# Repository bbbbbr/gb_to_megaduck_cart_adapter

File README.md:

# Game Boy to MegaDuck Cart Slot Adapter
Design files for a plug-in adapter to use Game Boy cartridges on a MegaDuck console.

The consoles have near identical cpu cores (1) and an almost identical cart pinout but a different edge connector style (Game Boy: one-sided, MegaDuck double-sided) and different cartridge widths (MegaDuck cart slot is narrower). This adapter allows plugging GB carts into the MegaDuck Console.

*1. But with modified register addresses, values and other changes to make the MegaDuck incompatible.

# Game Boy game compatibility
- **Q:** Does this mean regular Game Boy carts/games will run unmodified on the Mega Duck with this adapter?
- **A:** __No.__ Game Boy games require manual ROM patching to alter their register addresses, values and other changes in order to run on the Mega Duck.

# Why?
Flash carts for the Game Boy are easier to obtain and are available with a wider variety of features than those for the MegaDuck. Having access to the full range of GB flash carts opens up a lot of options for Mega Duck homebrew development, research and testing. This includes Game Boy Cameras modified to allow running custom ROMs run on them.

# Cartridge Shell
The following 3D printable cartidge shell design can be used with this adapter if the top edge of it is either removed from the design before printing or manually trimmed after printing.

https://github.com/bbbbbr/megaduck_cartridge_shell

TODO: Make cart shell specicially meant for this adapter

# Riser Height
The design has been built with **11mm risers** which provides enough clearance to plug in a some [GB Interceptor](https://github.com/bbbbbr/megaduck-interceptor) builds.

Riser heights down to **3.5mm - 4mm** should work and would result in a much smaller gap between the cart and the back of the console.

# License
Per the LICENSE file this design is released into the public domain and no attribution is required.

# Credits & Thanks
Thanks to Sean Riddle, Nitro2k, TexElec (pcb design)

# Alternate Top Board for Game Boy Camera
A different top board that allows using a regular Game Boy Camera Shell (modified ROM still required) is also available.
It changes the orientation so the Game Boy cart connector is facing UP.

The design is by Raphaël Boichot: https://github.com/Raphael-Boichot/Megaduck-to-game-boy-camera-adapter

# Pix

# GB to MegaDuck Cart Edge Connector Pinout Mapping

| **Mega Duck Cart Side** | **Pin Num** | **GB/DMG Pin** | **Mega Duck Pin** |
| ----------------------- | ----------- | -------------- | ----------------- |
| top                     | 1           | VCC            | +5 VDC            |
| bottom                  | 2           | CLK            | CLK               |
| top                     | 3           | /WR            | /WR               |
| bottom                  | 4           | /RD            | /RD               |
| top                     | 5           | CS             | CS                |
| bottom                  | 6           | A0             | A0                |
| top                     | 7           | A1             | A1                |
| bottom                  | 8           | A2             | A2                |
| top                     | 9           | A3             | A3                |
| bottom                  | 10          | A4             | A4                |
| top                     | 11          | A5             | A5                |
| bottom                  | 12          | A6             | A6                |
| top                     | 13          | A7             | A7                |
| bottom                  | 14          | A8             | A8                |
| top                     | 15          | A9             | A9                |
| bottom                  | 16          | A10            | A10               |
| top                     | 17          | A11            | A11               |
| bottom                  | 18          | A12            | A12               |
| top                     | 19          | A13            | A13               |
| bottom                  | 20          | A14            | A14               |
| top                     | 21          | A15            | A15               |
| bottom                  | 22          | D0             | D0                |
| top                     | 23          | D1             | D1                |
| bottom                  | 24          | D2             | D2                |
| top                     | 25          | D3             | D3                |
| bottom                  | 26          | D4             | D4                |
| top                     | 27          | D5             | D5                |
| bottom                  | 28          | D6             | D6                |
| top                     | 29          | D7             | D7                |
| bottom                  | 30          | /RST           | /RST              |
| top                     | 31          | VIN            | NC                |
| bottom                  | 32          | GND            | NC                |
| top                     | 33          | \-             | NC                |
| bottom                  | 34          | \-             | NC                |
| top                     | 35          | \-             | GND               |
| bottom                  | 36          | \-             | GND               |

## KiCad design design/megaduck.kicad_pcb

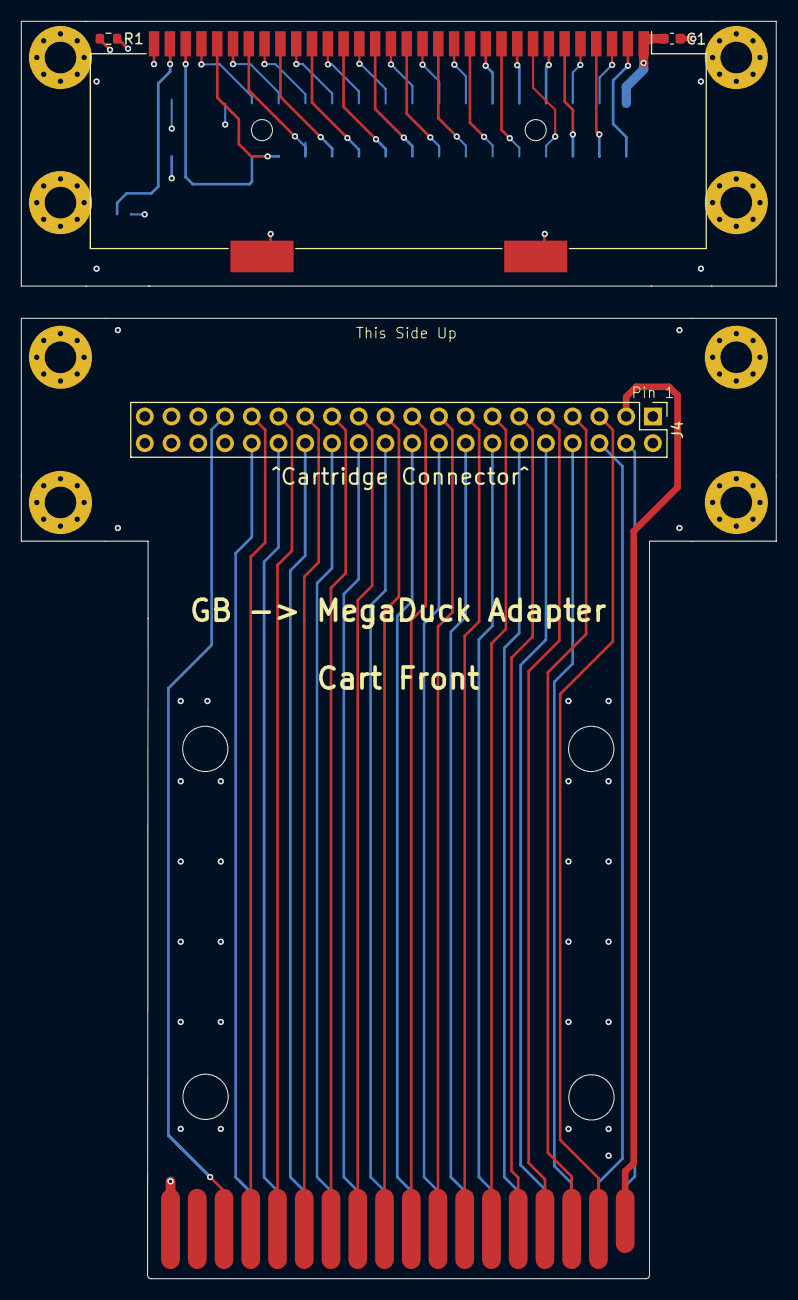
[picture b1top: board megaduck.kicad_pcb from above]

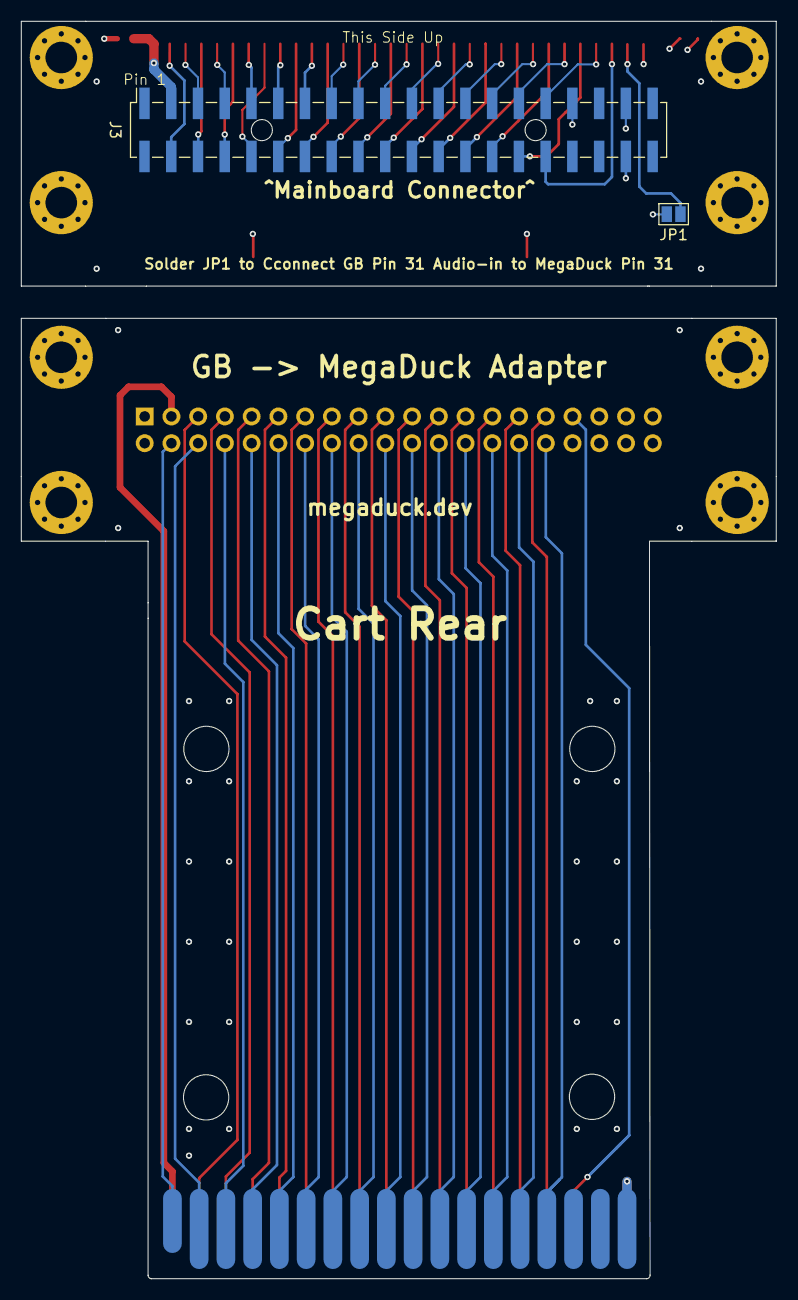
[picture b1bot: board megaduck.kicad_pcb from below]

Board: 4 copper layers, 71.7 x 119.4 mm, 15 parts (2 on the bottom side), 33 nets.

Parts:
C1: 0.1uf; C_0603_1608Metric
H1, H2, H3, H4, H5, H6, H7, H8: MountingHole_Pad; MountingHole_3mm_Pad_Via
J1: Conn_02x18_Odd_Even; Mega_Duck_36_Pin
J3: GameBoy_Cartridge_MountingPin; GameBoy_Cartridge_AGS_1x32-1MP_P1.50mm_Socket_Horizontal
J3#2: Conn_02x20_Odd_Even; PinSocket_2x20_P2.54mm_Vertical_SMD
J4: Conn_02x20_Odd_Even; PinHeader_2x20_P2.54mm_Vertical
JP1: SolderJumper_2_Open; SolderJumper-2_P1.3mm_Open_Pad1.0x1.5mm
R1: 100k; R_0603_1608Metric

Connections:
/A0: J1.6, J3.6 (A0), J3#2.8, J4.8
/A1: J1.7, J3.7 (A1), J3#2.9, J4.9
/A2: J1.8, J3.8 (A2), J3#2.10, J4.10
/A3: J1.9, J3.9 (A3), J3#2.11, J4.11
/A4: J1.10, J3.10 (A4), J3#2.12, J4.12
/A5: J1.11, J3.11 (A5), J3#2.13, J4.13
/A6: J1.12, J3.12 (A6), J3#2.14, J4.14
/A7: J1.13, J3.13 (A7), J3#2.15, J4.15
/A8: J1.14, J3.14 (A8), J3#2.16, J4.16
/A9: J1.15, J3.15 (A9), J3#2.17, J4.17
/A10: J1.16, J3.16 (A10), J3#2.18, J4.18
/A11: J1.17, J3.17 (A11), J3#2.19, J4.19
/A12: J1.18, J3.18 (A12), J3#2.20, J4.20
/A13: J1.19, J3.19 (A13), J3#2.21, J4.21
/A14: J1.20, J3.20 (A14), J3#2.22, J4.22
/A15: J1.21, J3.21 (A15), J3#2.23, J4.23
/D0: J1.22, J3.22 (D0), J3#2.24, J4.24
/D1: J1.23, J3.23 (D1), J3#2.25, J4.25
/D2: J1.24, J3.24 (D2), J3#2.26, J4.26
/D3: J1.25, J3.25 (D3), J3#2.27, J4.27
/D4: J1.26, J3.26 (D4), J3#2.28, J4.28
/D5: J1.27, J3.27 (D5), J3#2.29, J4.29
/D6: J1.28, J3.28 (D6), J3#2.30, J4.30
/D7: J1.29, J3.29 (D7), J3#2.31, J4.31
/PHI: J1.2, J3.2 (PHI), J3#2.4, J4.4
/VCC: C1.1, J1.1, J3.1 (VCC), J3#2.3, J4.3, R1.1
/VIN+: J1.31, J3#2.33, J4.33, JP1.1 (A)
/~CS: J1.5, J3.5 (~CS), J3#2.7, J4.7
/~RD: J1.4, J3.4 (~RD), J3#2.6, J4.6
/~RES: J1.30, J3.30 (~RES), J3#2.32, J4.32, R1.2
/~WR: J1.3, J3.3 (~WR), J3#2.5, J4.5
GND: C1.2, H1.1, H2.1, H3.1, H4.1, H5.1, H6.1, H7.1, H8.1, J1.35, J1.36, J3.32 (GND), J3.MP, J3#2.37, J3#2.38, J4.37, J4.38
unnamed: J3.31 (VIN), JP1.2 (B)

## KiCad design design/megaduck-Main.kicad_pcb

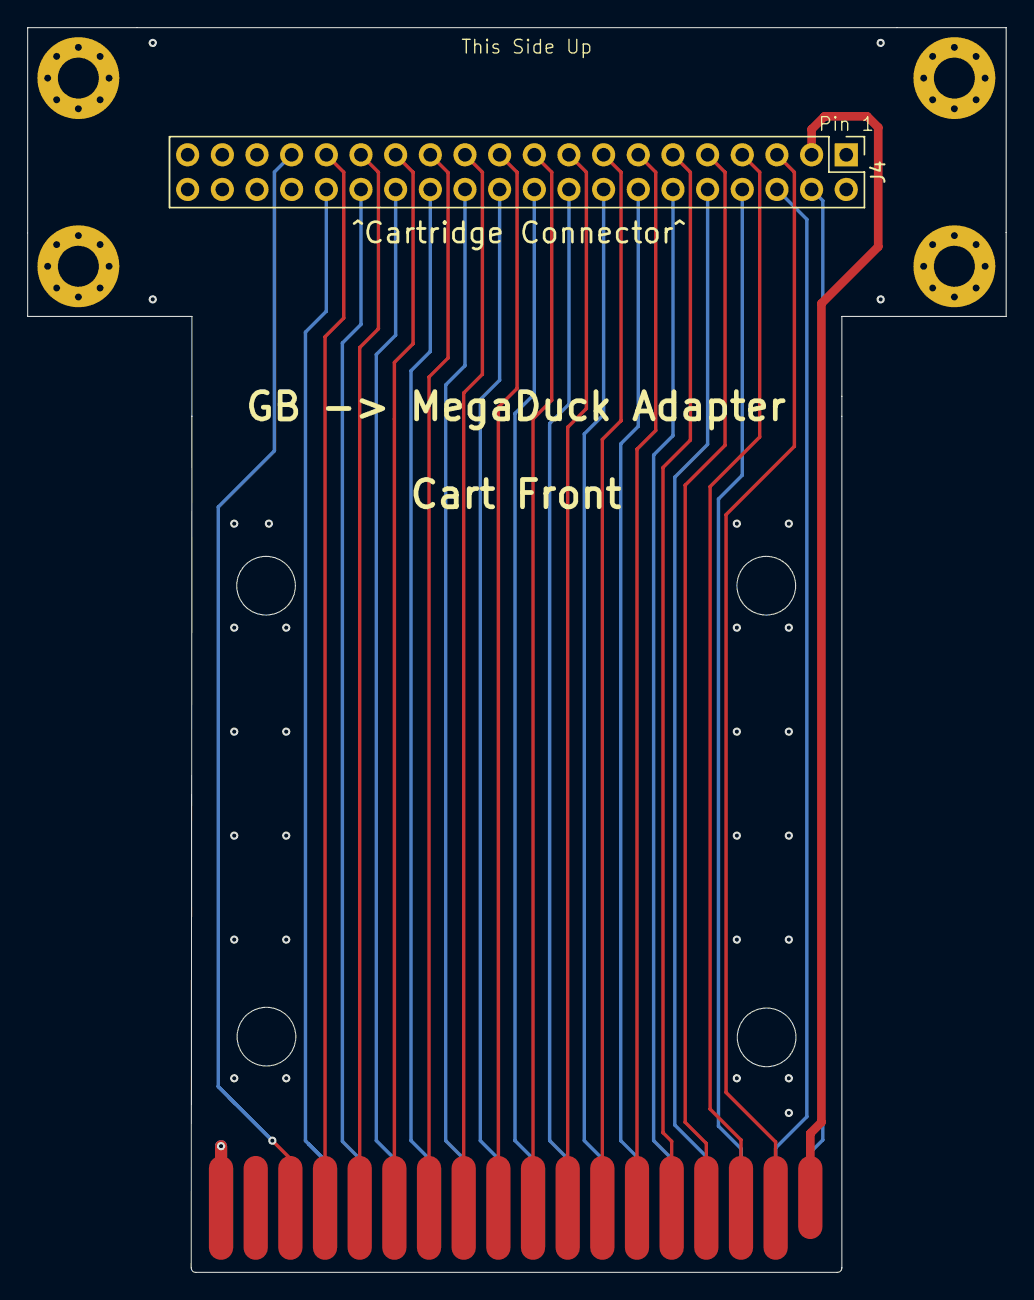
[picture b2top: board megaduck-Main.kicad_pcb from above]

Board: 4 copper layers, 71.7 x 91.2 mm, 6 parts (0 on the bottom side), 32 nets.

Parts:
H3, H4, H7, H8: MountingHole_Pad; MountingHole_3mm_Pad_Via
J1: Conn_02x18_Odd_Even; Mega_Duck_36_Pin
J4: Conn_02x20_Odd_Even; PinHeader_2x20_P2.54mm_Vertical

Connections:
/A0: J1.6, J4.8
/A1: J1.7, J4.9
/A2: J1.8, J4.10
/A3: J1.9, J4.11
/A4: J1.10, J4.12
/A5: J1.11, J4.13
/A6: J1.12, J4.14
/A7: J1.13, J4.15
/A8: J1.14, J4.16
/A9: J1.15, J4.17
/A10: J1.16, J4.18
/A11: J1.17, J4.19
/A12: J1.18, J4.20
/A13: J1.19, J4.21
/A14: J1.20, J4.22
/A15: J1.21, J4.23
/D0: J1.22, J4.24
/D1: J1.23, J4.25
/D2: J1.24, J4.26
/D3: J1.25, J4.27
/D4: J1.26, J4.28
/D5: J1.27, J4.29
/D6: J1.28, J4.30
/D7: J1.29, J4.31
/PHI: J1.2, J4.4
/VCC: J1.1, J4.3
/VIN+: J1.31, J4.33
/~CS: J1.5, J4.7
/~RD: J1.4, J4.6
/~RES: J1.30, J4.32
/~WR: J1.3, J4.5
GND: H3.1, H4.1, H7.1, H8.1, J1.35, J1.36, J4.37, J4.38

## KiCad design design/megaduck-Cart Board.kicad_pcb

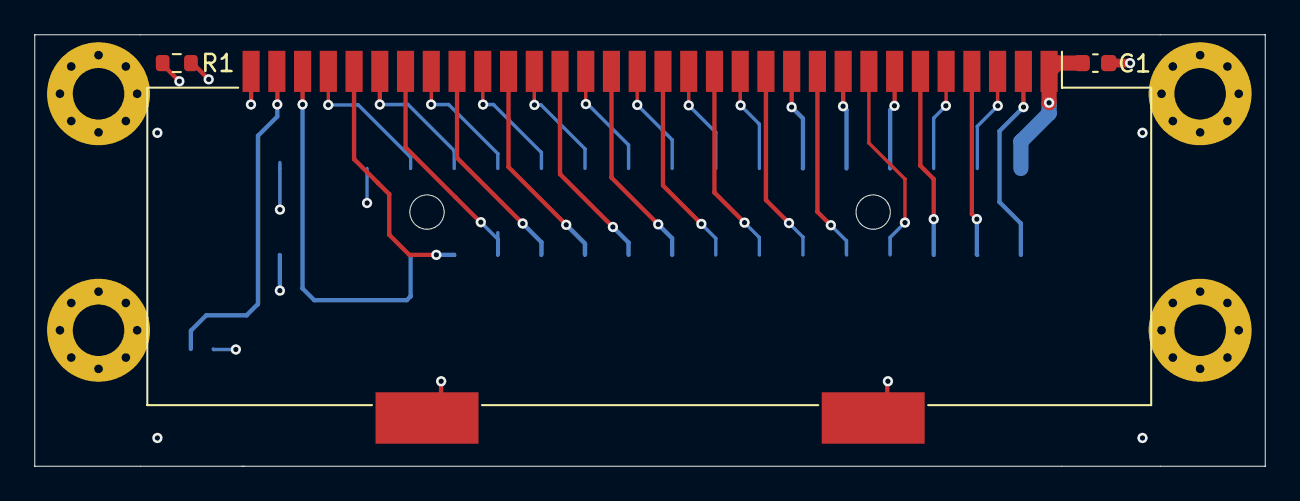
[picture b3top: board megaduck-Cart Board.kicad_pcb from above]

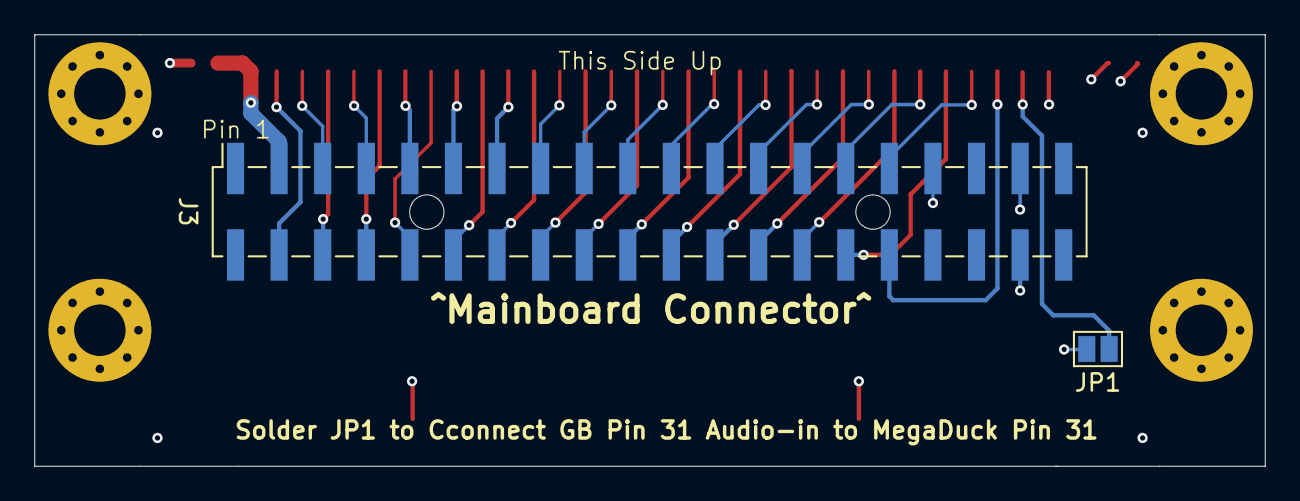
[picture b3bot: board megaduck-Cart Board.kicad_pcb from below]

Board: 4 copper layers, 71.7 x 25.1 mm, 9 parts (2 on the bottom side), 33 nets.

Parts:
C1: 0.1uf; C_0603_1608Metric
H1, H2, H5, H6: MountingHole_Pad; MountingHole_3mm_Pad_Via
J3: GameBoy_Cartridge_MountingPin; GameBoy_Cartridge_AGS_1x32-1MP_P1.50mm_Socket_Horizontal
J3#2: Conn_02x20_Odd_Even; PinSocket_2x20_P2.54mm_Vertical_SMD
JP1: SolderJumper_2_Open; SolderJumper-2_P1.3mm_Open_Pad1.0x1.5mm
R1: 100k; R_0603_1608Metric

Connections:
/A0: J3.6 (A0), J3#2.8
/A1: J3.7 (A1), J3#2.9
/A2: J3.8 (A2), J3#2.10
/A3: J3.9 (A3), J3#2.11
/A4: J3.10 (A4), J3#2.12
/A5: J3.11 (A5), J3#2.13
/A6: J3.12 (A6), J3#2.14
/A7: J3.13 (A7), J3#2.15
/A8: J3.14 (A8), J3#2.16
/A9: J3.15 (A9), J3#2.17
/A10: J3.16 (A10), J3#2.18
/A11: J3.17 (A11), J3#2.19
/A12: J3.18 (A12), J3#2.20
/A13: J3.19 (A13), J3#2.21
/A14: J3.20 (A14), J3#2.22
/A15: J3.21 (A15), J3#2.23
/D0: J3.22 (D0), J3#2.24
/D1: J3.23 (D1), J3#2.25
/D2: J3.24 (D2), J3#2.26
/D3: J3.25 (D3), J3#2.27
/D4: J3.26 (D4), J3#2.28
/D5: J3.27 (D5), J3#2.29
/D6: J3.28 (D6), J3#2.30
/D7: J3.29 (D7), J3#2.31
/PHI: J3.2 (PHI), J3#2.4
/VCC: C1.1, J3.1 (VCC), J3#2.3, R1.1
/VIN+: J3#2.33, JP1.1 (A)
/~CS: J3.5 (~CS), J3#2.7
/~RD: J3.4 (~RD), J3#2.6
/~RES: J3.30 (~RES), J3#2.32, R1.2
/~WR: J3.3 (~WR), J3#2.5
GND: C1.2, H1.1, H2.1, H5.1, H6.1, J3.32 (GND), J3.MP, J3#2.37, J3#2.38
unnamed: J3.31 (VIN), JP1.2 (B)

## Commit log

2025-01-25 Add design files and pix
2025-01-25 Populate Readme with info about project
2025-01-25 Pix: fix rear pcb pic
2025-01-25 Add note about riser height
2025-09-29 Mention and link to alternate top board
